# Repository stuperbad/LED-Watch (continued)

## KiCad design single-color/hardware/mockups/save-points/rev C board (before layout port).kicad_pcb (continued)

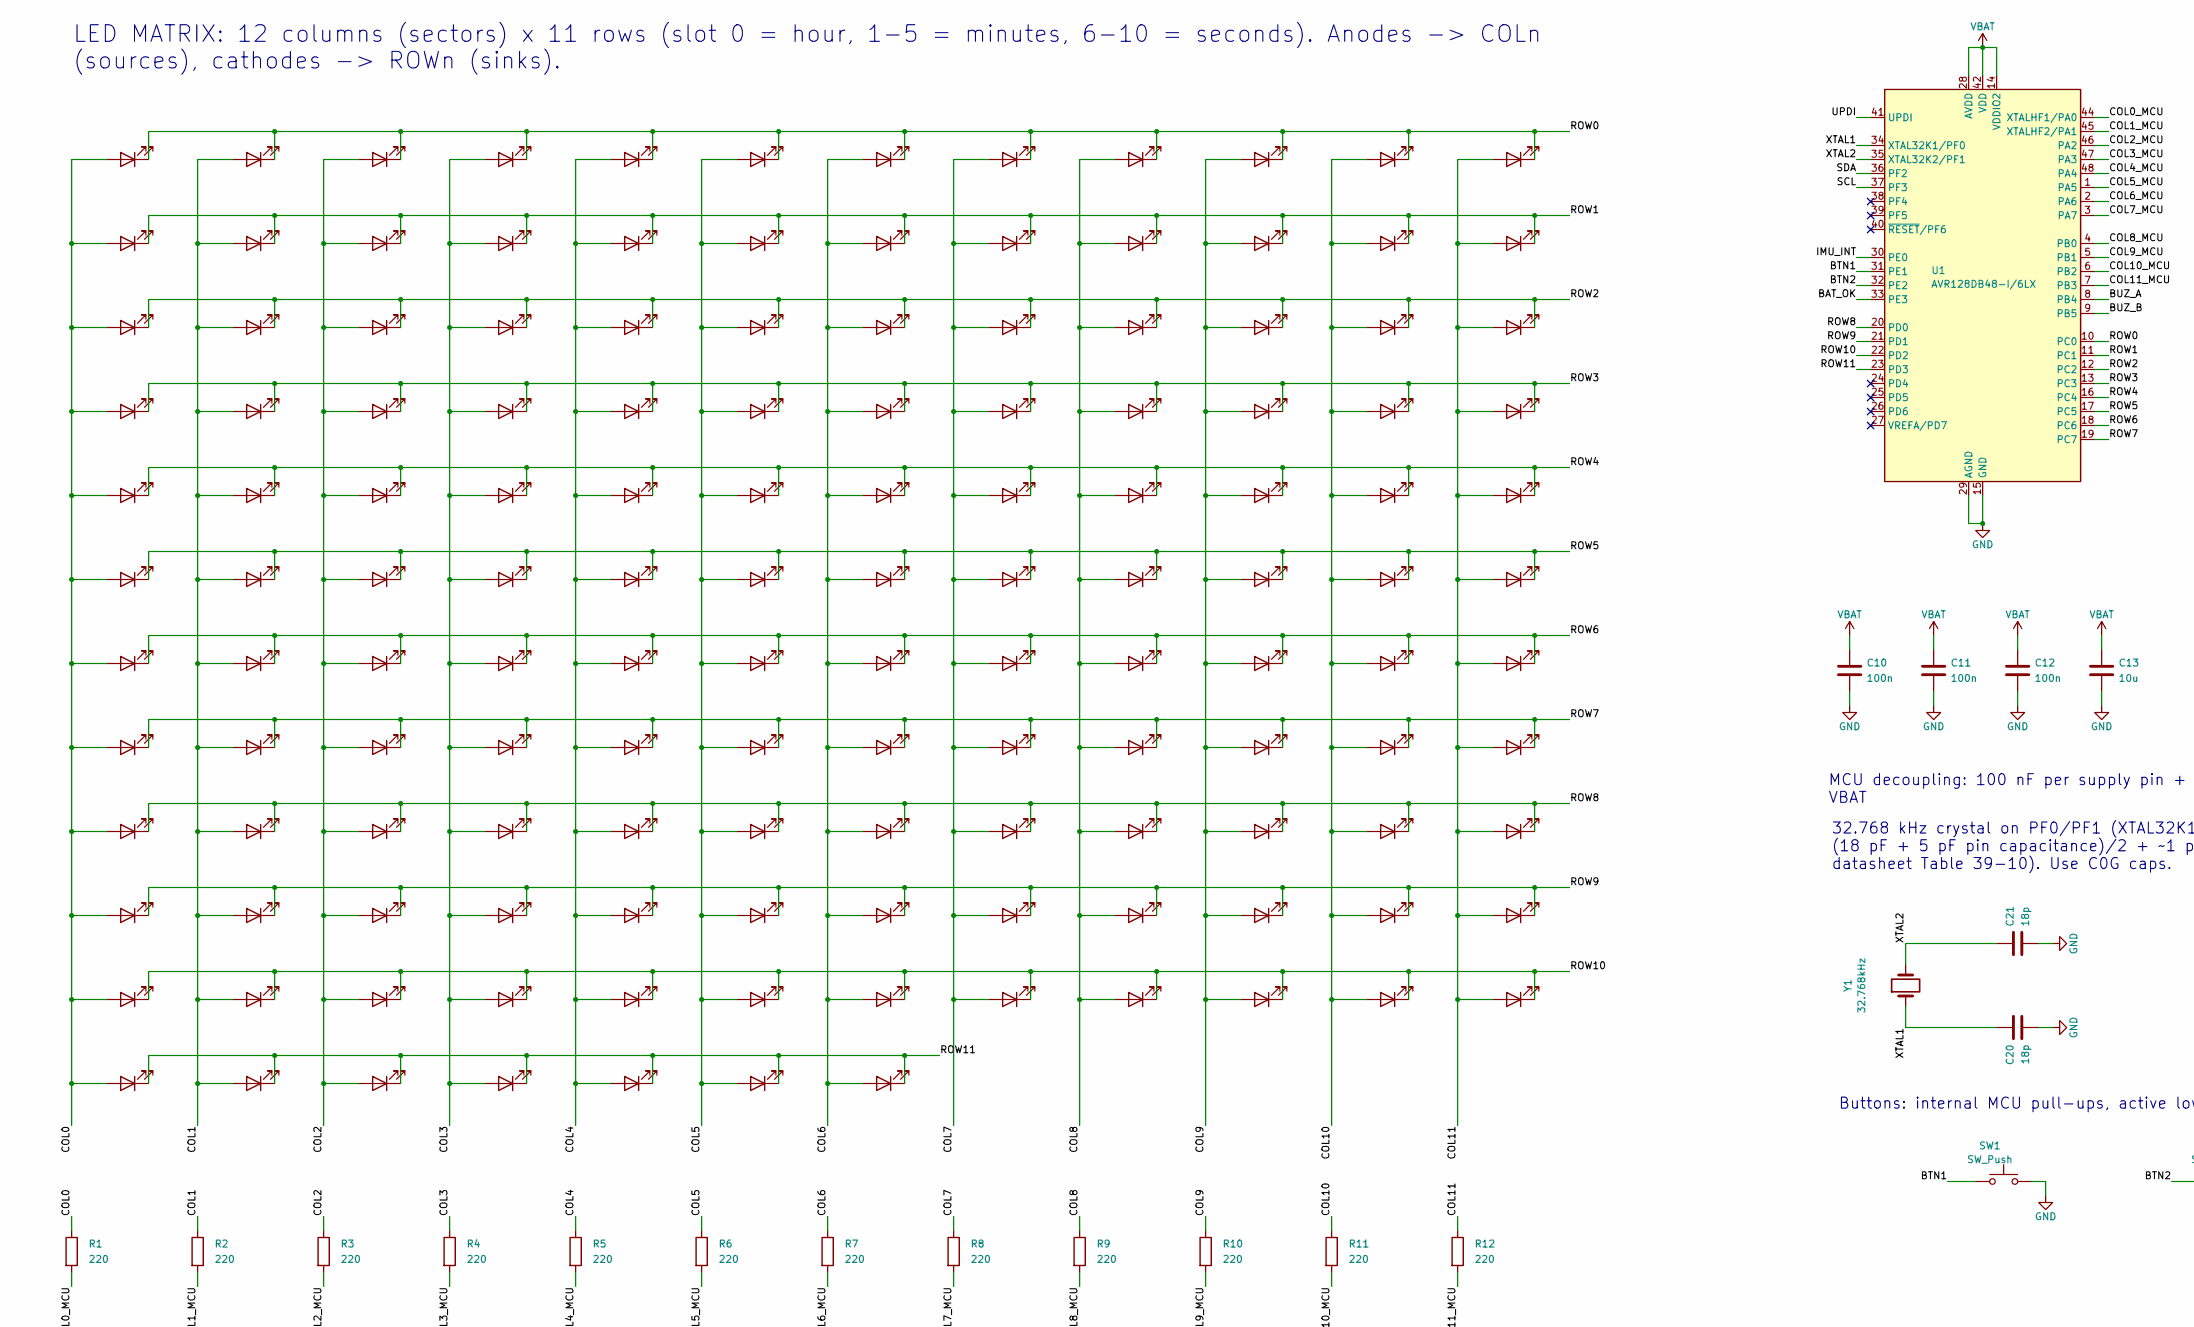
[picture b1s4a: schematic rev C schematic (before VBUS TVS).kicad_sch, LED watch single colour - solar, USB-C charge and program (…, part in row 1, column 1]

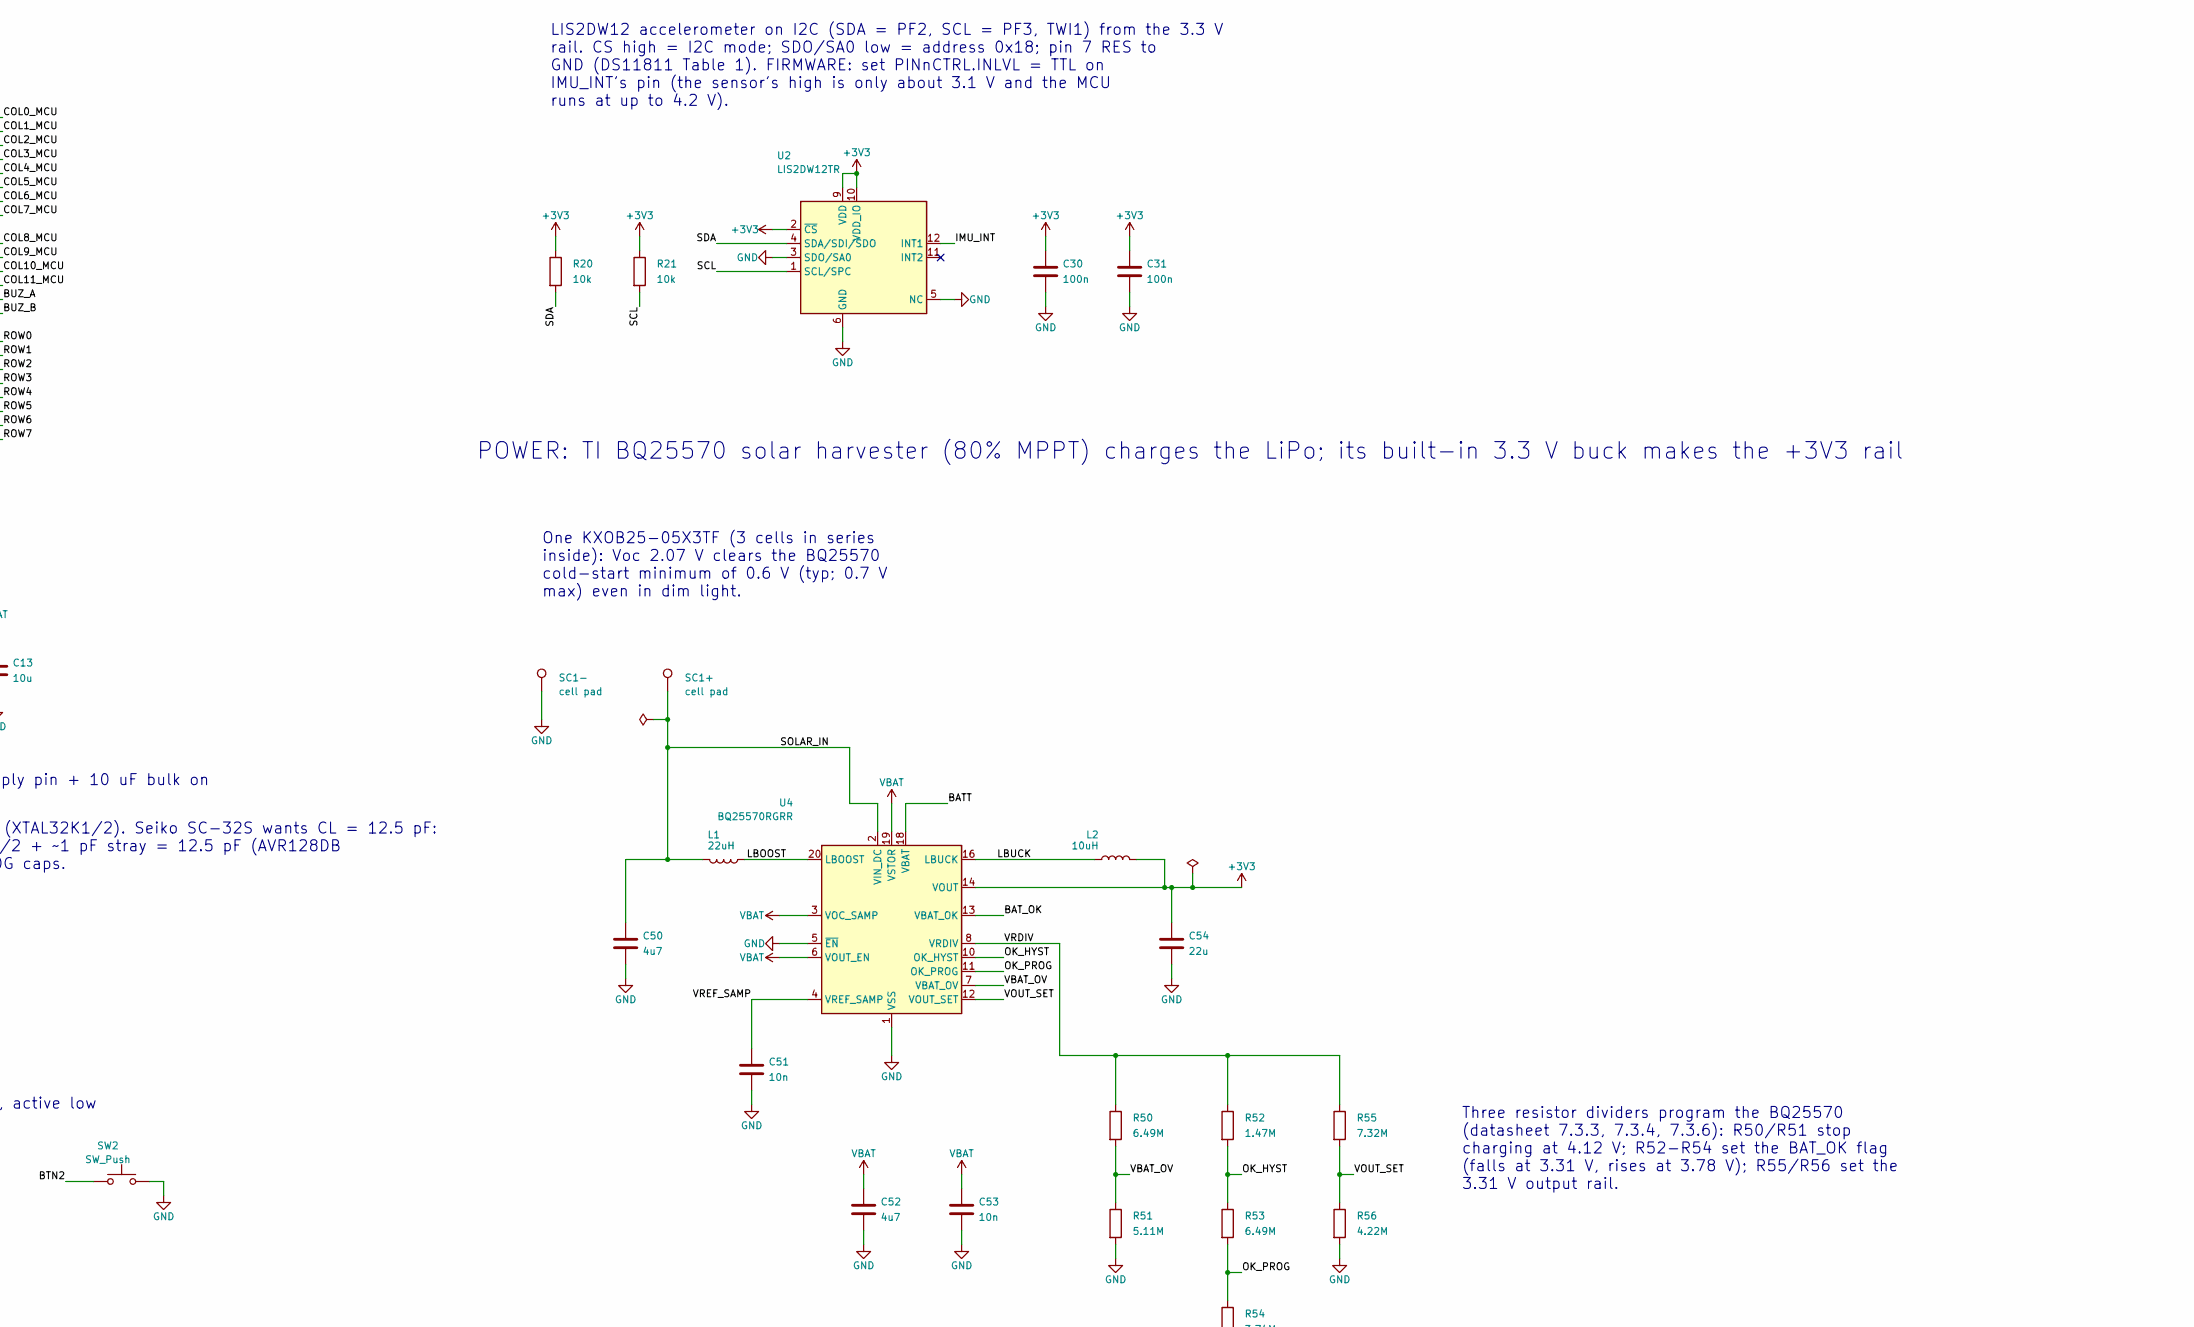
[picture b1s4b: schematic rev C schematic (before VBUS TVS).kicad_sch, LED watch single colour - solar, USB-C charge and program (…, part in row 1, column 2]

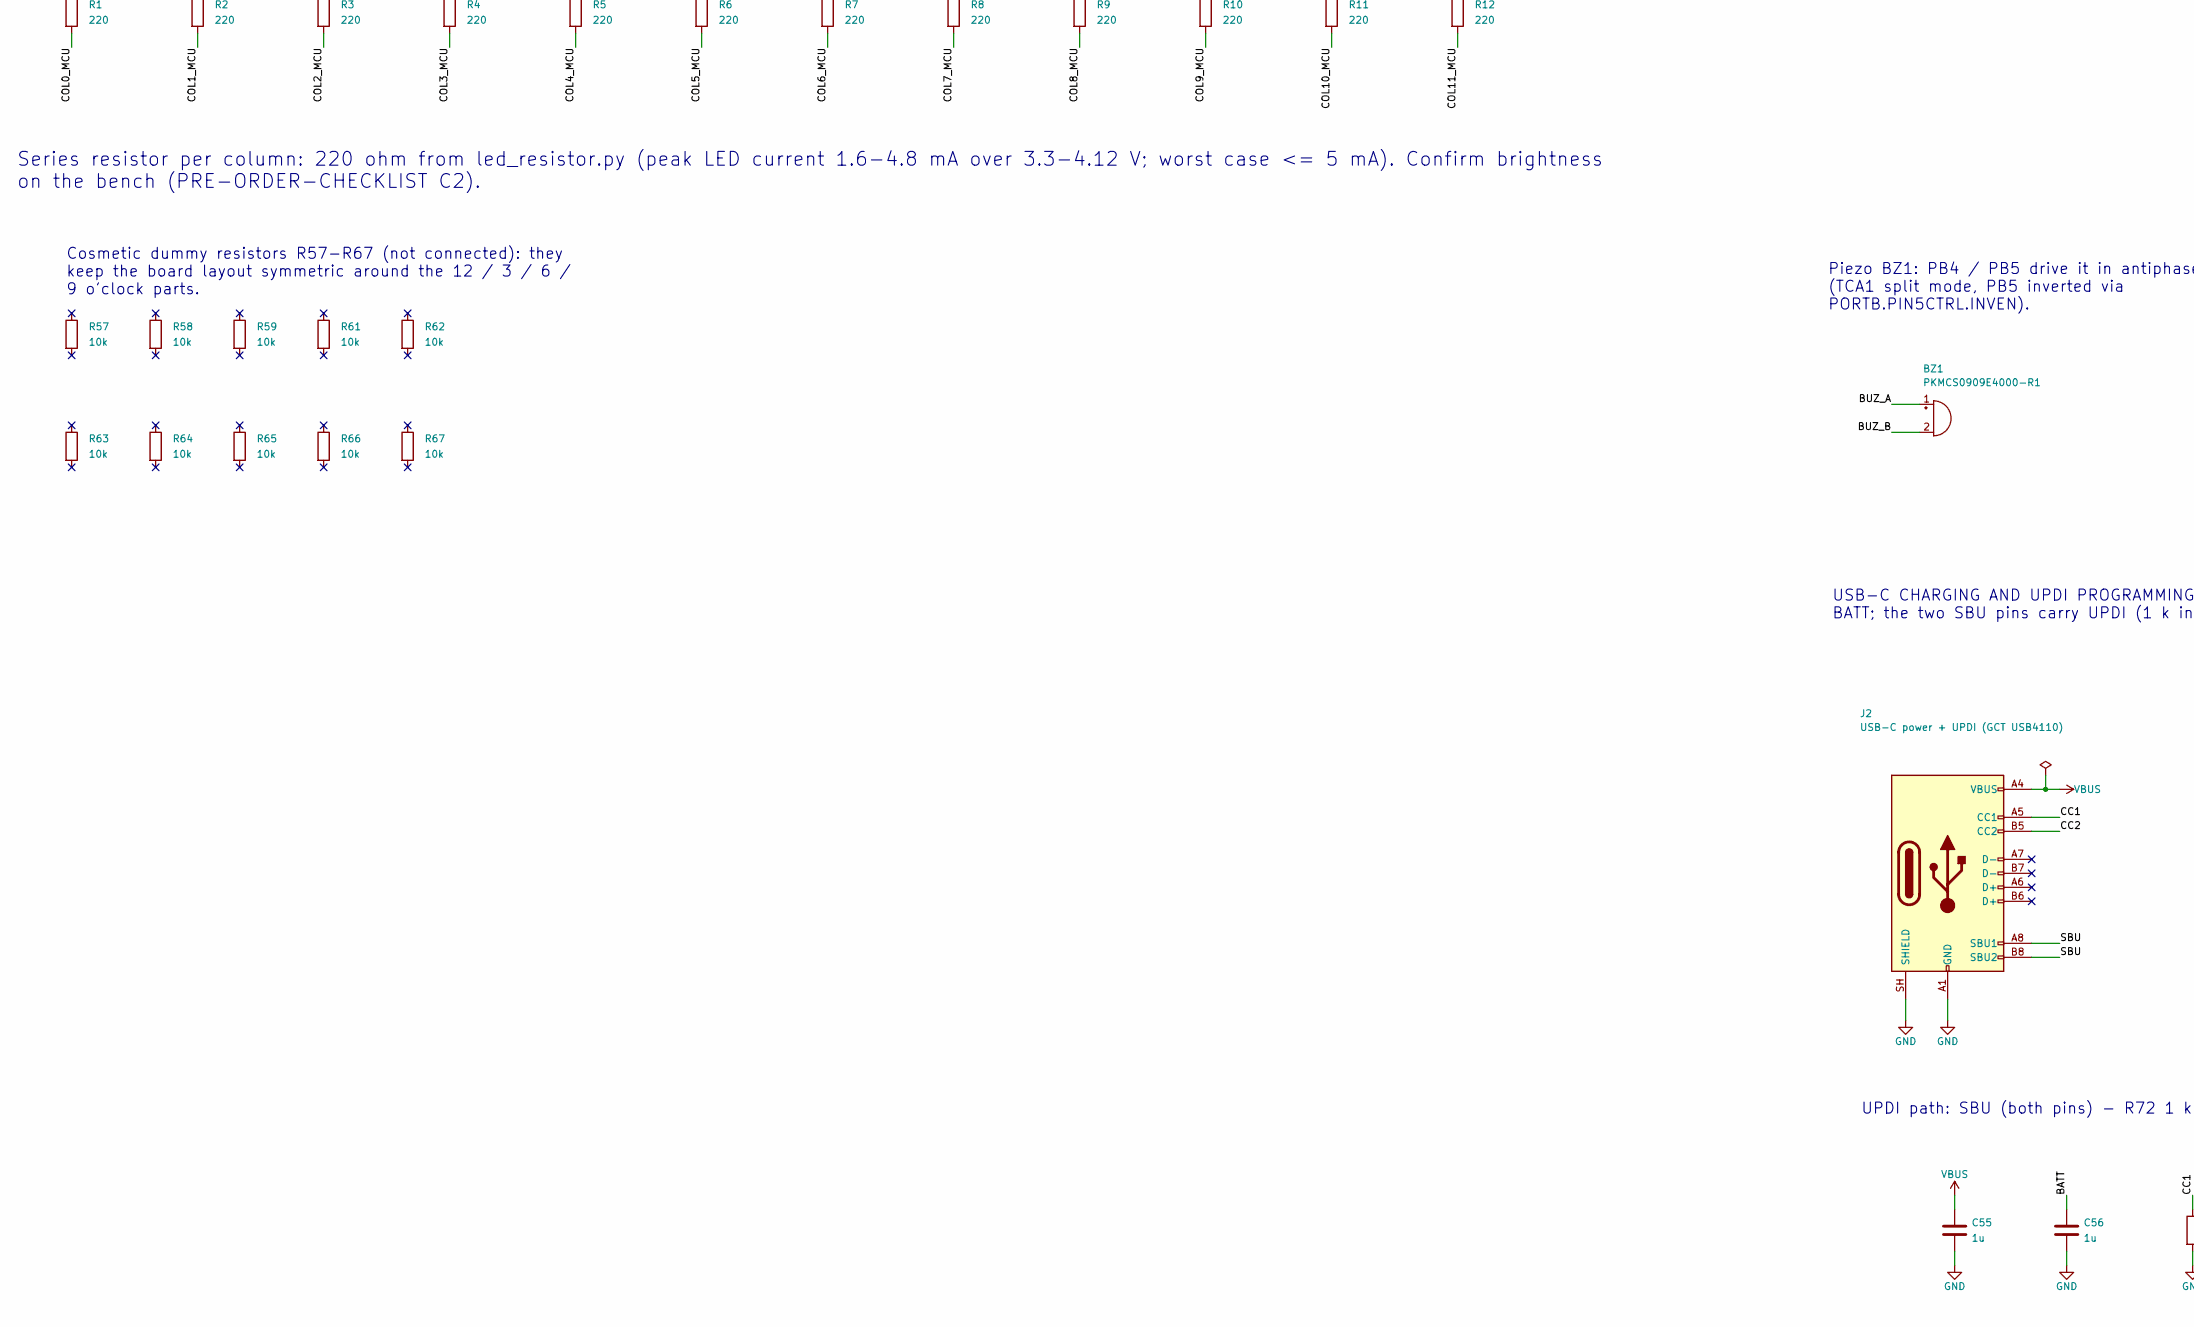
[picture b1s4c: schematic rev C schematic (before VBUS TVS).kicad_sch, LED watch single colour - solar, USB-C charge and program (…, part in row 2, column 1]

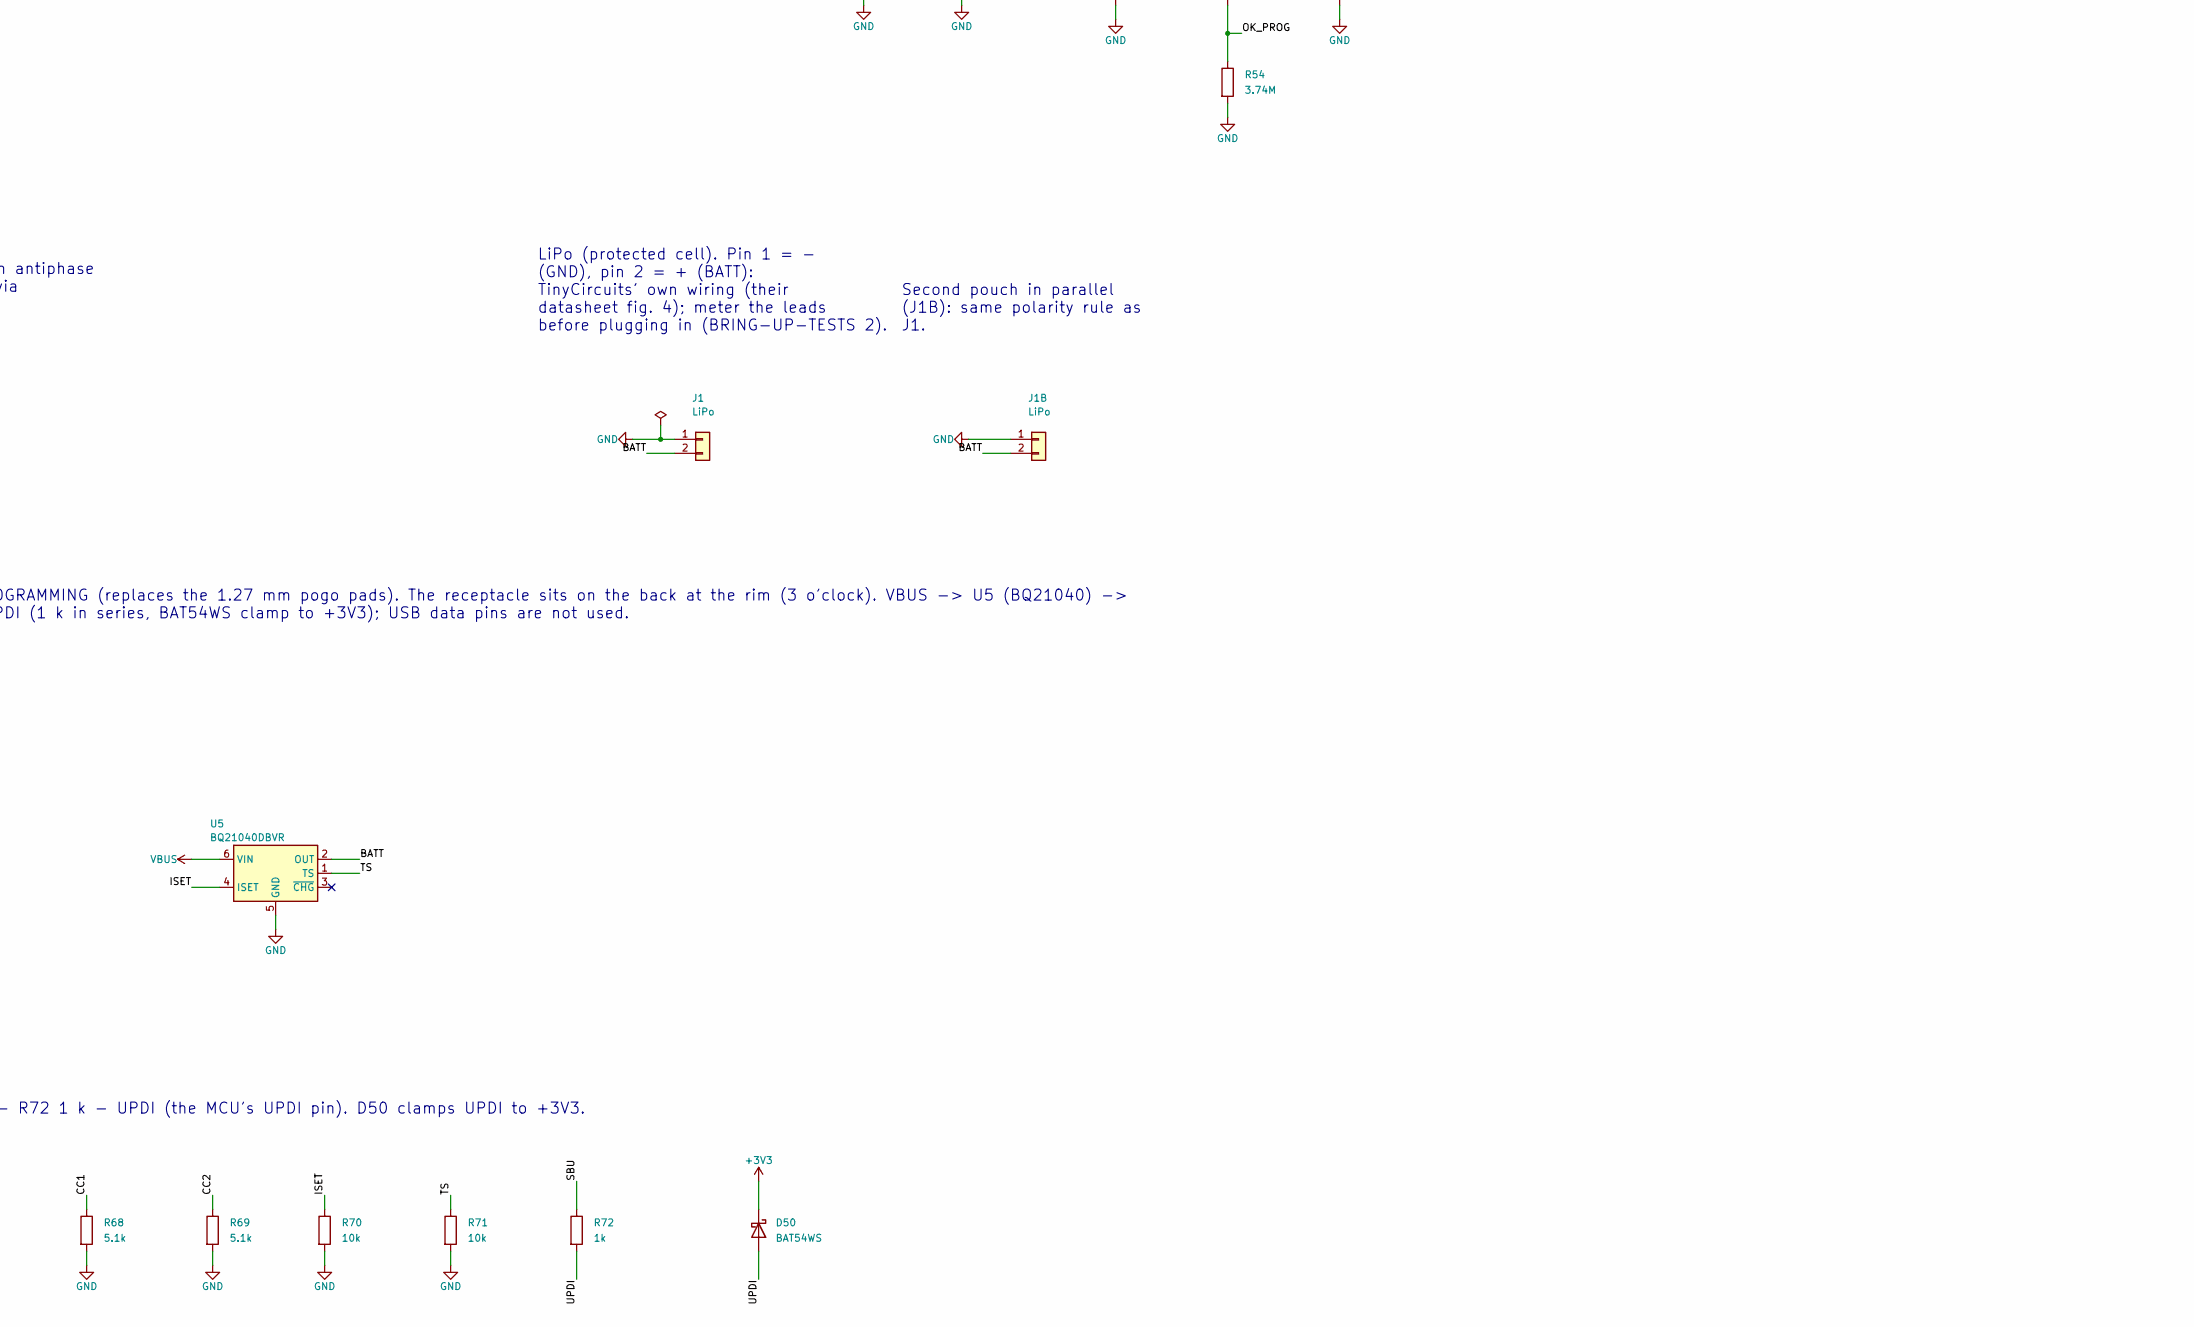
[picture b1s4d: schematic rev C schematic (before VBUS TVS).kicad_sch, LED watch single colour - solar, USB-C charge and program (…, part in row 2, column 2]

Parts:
BZ1: PKMCS0909E4000-R1; Piezo_Murata_PKMCS0909E4000-R1_9x9mm; MPN PKMCS0909E4000-R1; LCSC C910763
C10, C11, C12, C30, C31: 100n; C_0402_1005Metric
C13: 10u; C_0402_1005Metric
C20, C21: 18p; C_0402_1005Metric
C50, C52: 4u7; C_0402_1005Metric
C51, C53: 10n; C_0402_1005Metric
C54: 22u; C_0805_2012Metric
C55, C56: 1u; C_0402_1005Metric; LCSC C52923
D50: BAT54WS; D_SOD-323; MPN BAT54WS; LCSC C304155
H1, H2, H3, H4, H5, H6, H7, H8, H9, H10, H11, H12: LED white 0603; LED_0603_1608Metric
IND1: SET; LED_0402_1005Metric
IND2: TMR; LED_0402_1005Metric
IND3: BAT; LED_0402_1005Metric
IND4: FUN; LED_0402_1005Metric
IND5: CFG; LED_0402_1005Metric
IND6: LCK; LED_0402_1005Metric
IND7: ALM; LED_0402_1005Metric
J1, J1B: LiPo; JST_SH_SM02B-SRSS-TB_1x02-1MP_P1.00mm_Horizontal
J2: USB-C power + UPDI (GCT USB4110); USB_C_Receptacle_GCT_USB4110; MPN USB4110-GF-A
L1: 22uH; L_1210_3225Metric
L2: 10uH; L_1210_3225Metric
M0, M1, M2, M3, M4, M5, M6, M7, M8, M9, M10, M11, M12, M13, M14, M15, M16, M17, M18, M19, M20, M21, M22, M23, M24, M25, M26, M27, M28, M29, M30, M31, M32, M33, M34, M35, M36, M37, M38, M39, M40, M41, M42, M43, M44, M45, M46, M47, M48, M49, M50, M51, M52, M53, M54, M55, M56, M57, M58, M59: LED white 0402; LED_0402_1005Metric
R1, R2, R3, R4, R5, R6, R7, R8, R9, R10, R11, R12: 220; R_0402_1005Metric
R20, R21, R57, R58, R59, R61, R62, R63, R64, R65, R66, R67: 10k; R_0402_1005Metric
R50, R53: 6.49M; R_0402_1005Metric
R51: 5.11M; R_0402_1005Metric
R52: 1.47M; R_0402_1005Metric
R54: 3.74M; R_0402_1005Metric
R55: 7.32M; R_0402_1005Metric
R56: 4.22M; R_0402_1005Metric
R68, R69: 5.1k; R_0402_1005Metric; LCSC C25905
R70, R71: 10k; R_0402_1005Metric; LCSC C25744
R72: 1k; R_0402_1005Metric; LCSC C11702
S0, S1, S2, S3, S4, S5, S6, S7, S8, S9, S10, S11, S12, S13, S14, S15, S16, S17, S18, S19, S20, S21, S22, S23, S24, S25, S26, S27, S28, S29, S30, S31, S32, S33, S34, S35, S36, S37, S38, S39, S40, S41, S42, S43, S44, S45, S46, S47, S48, S49, S50, S51, S52, S53, S54, S55, S56, S57, S58, S59: LED white 0201; LED_0201_0603Metric
SC1+, SC1-: cell pad; KXOB25_cell_pad_2.5x7.4mm
SW1, SW2: SW_Push; SW_Push_1P1T_NO_CK_KMR2
U1: AVR128DB48-I/6LX; QFN-48-1EP_6x6mm_P0.4mm_EP4.2x4.2mm
U2: LIS2DW12TR; LGA-12_2x2mm_P0.5mm; MPN LIS2DW12TR
U4: BQ25570RGRR; BQ25570RGR_VQFN-20_3.5x3.5mm_P0.5mm_EP2.05mm
U5: BQ21040DBVR; SOT-23-6; MPN BQ21040DBVR; LCSC C202311
Y1: 32.768kHz; Crystal_SMD_3215-2Pin_3.2x1.5mm; MPN ABS07-32.768KHZ-T

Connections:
+3V3: C30.1, C31.1, C54.1, D50.1 (K), L2.2, R20.1, R21.1, U2.2 (~CS), U2.9 (VDD), U2.10 (VDD_IO), U4.14 (VOUT)
/BATT: C56.1, J1.2, J1B.2, U4.18 (VBAT), U5.2 (OUT)
/BAT_OK: U1.33 (PE3), U4.13 (VBAT_OK)
/BTN1: SW1.1, U1.31 (PE1)
/BTN2: SW2.1, U1.32 (PE2)
/BUZ_A: BZ1.1 (+), U1.8 (PB4)
/BUZ_B: BZ1.2 (-), U1.9 (PB5)
/CC1: J2.A5 (CC1), R68.1
/CC2: J2.B5 (CC2), R69.1
/COL0: H12.2 (A), IND1.2 (A), M0.2 (A), M1.2 (A), M2.2 (A), M3.2 (A), M4.2 (A), R1.1, S0.2 (A), S1.2 (A), S2.2 (A), S3.2 (A), S4.2 (A)
/COL0_MCU: R1.2, U1.44 (XTALHF1/PA0)
/COL1: H1.2 (A), IND2.2 (A), M5.2 (A), M6.2 (A), M7.2 (A), M8.2 (A), M9.2 (A), R2.1, S5.2 (A), S6.2 (A), S7.2 (A), S8.2 (A), S9.2 (A)
/COL1_MCU: R2.2, U1.45 (XTALHF2/PA1)
/COL2: H2.2 (A), IND3.2 (A), M10.2 (A), M11.2 (A), M12.2 (A), M13.2 (A), M14.2 (A), R3.1, S10.2 (A), S11.2 (A), S12.2 (A), S13.2 (A), S14.2 (A)
/COL2_MCU: R3.2, U1.46 (PA2)
/COL3: H3.2 (A), IND4.2 (A), M15.2 (A), M16.2 (A), M17.2 (A), M18.2 (A), M19.2 (A), R4.1, S15.2 (A), S16.2 (A), S17.2 (A), S18.2 (A), S19.2 (A)
/COL3_MCU: R4.2, U1.47 (PA3)
/COL4: H4.2 (A), IND5.2 (A), M20.2 (A), M21.2 (A), M22.2 (A), M23.2 (A), M24.2 (A), R5.1, S20.2 (A), S21.2 (A), S22.2 (A), S23.2 (A), S24.2 (A)
/COL4_MCU: R5.2, U1.48 (PA4)
/COL5: H5.2 (A), IND6.2 (A), M25.2 (A), M26.2 (A), M27.2 (A), M28.2 (A), M29.2 (A), R6.1, S25.2 (A), S26.2 (A), S27.2 (A), S28.2 (A), S29.2 (A)
/COL5_MCU: R6.2, U1.1 (PA5)
/COL6: H6.2 (A), IND7.2 (A), M30.2 (A), M31.2 (A), M32.2 (A), M33.2 (A), M34.2 (A), R7.1, S30.2 (A), S31.2 (A), S32.2 (A), S33.2 (A), S34.2 (A)
/COL6_MCU: R7.2, U1.2 (PA6)
/COL7: H7.2 (A), M35.2 (A), M36.2 (A), M37.2 (A), M38.2 (A), M39.2 (A), R8.1, S35.2 (A), S36.2 (A), S37.2 (A), S38.2 (A), S39.2 (A)
/COL7_MCU: R8.2, U1.3 (PA7)
/COL8: H8.2 (A), M40.2 (A), M41.2 (A), M42.2 (A), M43.2 (A), M44.2 (A), R9.1, S40.2 (A), S41.2 (A), S42.2 (A), S43.2 (A), S44.2 (A)
/COL8_MCU: R9.2, U1.4 (PB0)
/COL9: H9.2 (A), M45.2 (A), M46.2 (A), M47.2 (A), M48.2 (A), M49.2 (A), R10.1, S45.2 (A), S46.2 (A), S47.2 (A), S48.2 (A), S49.2 (A)
/COL9_MCU: R10.2, U1.5 (PB1)
/COL10: H10.2 (A), M50.2 (A), M51.2 (A), M52.2 (A), M53.2 (A), M54.2 (A), R11.1, S50.2 (A), S51.2 (A), S52.2 (A), S53.2 (A), S54.2 (A)
/COL10_MCU: R11.2, U1.6 (PB2)
/COL11: H11.2 (A), M55.2 (A), M56.2 (A), M57.2 (A), M58.2 (A), M59.2 (A), R12.1, S55.2 (A), S56.2 (A), S57.2 (A), S58.2 (A), S59.2 (A)
/COL11_MCU: R12.2, U1.7 (PB3)
/IMU_INT: U1.30 (PE0), U2.12 (INT1)
/ISET: R70.1, U5.4 (ISET)
/LBOOST: L1.1, U4.20 (LBOOST)
/LBUCK: L2.1, U4.16 (LBUCK)
/OK_HYST: R52.2, R53.1, U4.10 (OK_HYST)
/OK_PROG: R53.2, R54.1, U4.11 (OK_PROG)
/ROW0: H1.1 (K), H2.1 (K), H3.1 (K), H4.1 (K), H5.1 (K), H6.1 (K), H7.1 (K), H8.1 (K), H9.1 (K), H10.1 (K), H11.1 (K), H12.1 (K), U1.10 (PC0)
/ROW1: M0.1 (K), M5.1 (K), M10.1 (K), M15.1 (K), M20.1 (K), M25.1 (K), M30.1 (K), M35.1 (K), M40.1 (K), M45.1 (K), M50.1 (K), M55.1 (K), U1.11 (PC1)
/ROW2: M1.1 (K), M6.1 (K), M11.1 (K), M16.1 (K), M21.1 (K), M26.1 (K), M31.1 (K), M36.1 (K), M41.1 (K), M46.1 (K), M51.1 (K), M56.1 (K), U1.12 (PC2)
/ROW3: M2.1 (K), M7.1 (K), M12.1 (K), M17.1 (K), M22.1 (K), M27.1 (K), M32.1 (K), M37.1 (K), M42.1 (K), M47.1 (K), M52.1 (K), M57.1 (K), U1.13 (PC3)
/ROW4: M3.1 (K), M8.1 (K), M13.1 (K), M18.1 (K), M23.1 (K), M28.1 (K), M33.1 (K), M38.1 (K), M43.1 (K), M48.1 (K), M53.1 (K), M58.1 (K), U1.16 (PC4)
/ROW5: M4.1 (K), M9.1 (K), M14.1 (K), M19.1 (K), M24.1 (K), M29.1 (K), M34.1 (K), M39.1 (K), M44.1 (K), M49.1 (K), M54.1 (K), M59.1 (K), U1.17 (PC5)
/ROW6: S0.1 (K), S5.1 (K), S10.1 (K), S15.1 (K), S20.1 (K), S25.1 (K), S30.1 (K), S35.1 (K), S40.1 (K), S45.1 (K), S50.1 (K), S55.1 (K), U1.18 (PC6)
/ROW7: S1.1 (K), S6.1 (K), S11.1 (K), S16.1 (K), S21.1 (K), S26.1 (K), S31.1 (K), S36.1 (K), S41.1 (K), S46.1 (K), S51.1 (K), S56.1 (K), U1.19 (PC7)
/ROW8: S2.1 (K), S7.1 (K), S12.1 (K), S17.1 (K), S22.1 (K), S27.1 (K), S32.1 (K), S37.1 (K), S42.1 (K), S47.1 (K), S52.1 (K), S57.1 (K), U1.20 (PD0)
/ROW9: S3.1 (K), S8.1 (K), S13.1 (K), S18.1 (K), S23.1 (K), S28.1 (K), S33.1 (K), S38.1 (K), S43.1 (K), S48.1 (K), S53.1 (K), S58.1 (K), U1.21 (PD1)
/ROW10: S4.1 (K), S9.1 (K), S14.1 (K), S19.1 (K), S24.1 (K), S29.1 (K), S34.1 (K), S39.1 (K), S44.1 (K), S49.1 (K), S54.1 (K), S59.1 (K), U1.22 (PD2)
/ROW11: IND1.1 (K), IND2.1 (K), IND3.1 (K), IND4.1 (K), IND5.1 (K), IND6.1 (K), IND7.1 (K), U1.23 (PD3)
/SBU: J2.A8 (SBU1), J2.B8 (SBU2), R72.1
/SCL: R21.2, U1.37 (PF3), U2.1 (SCL/SPC)
/SDA: R20.2, U1.36 (PF2), U2.4 (SDA/SDI/SDO)
/SOLAR_IN: C50.1, L1.2, SC1+.1, U4.2 (VIN_DC)
/TS: R71.1, U5.1 (TS)
/UPDI: D50.2 (A), R72.2, U1.41 (UPDI)
/VBAT_OV: R50.2, R51.1, U4.7 (VBAT_OV)
/VOUT_SET: R55.2, R56.1, U4.12 (VOUT_SET)
/VRDIV: R50.1, R52.1, R55.1, U4.8 (VRDIV)
/VREF_SAMP: C51.1, U4.4 (VREF_SAMP)
/XTAL1: C20.1, U1.34 (XTAL32K1/PF0), Y1.1
/XTAL2: C21.1, U1.35 (XTAL32K2/PF1), Y1.2
GND: C10.2, C11.2, C12.2, C13.2, C20.2, C21.2, C30.2, C31.2, C50.2, C51.2, C52.2, C53.2, C54.2, C55.2, C56.2, J1.1, J1B.1, J2.A1 (GND), J2.A12 (GND), J2.B1 (GND), J2.B12 (GND), J2.SH (SHIELD), R51.2, R54.2, R56.2, R68.2, R69.2, R70.2, R71.2, SC1-.1, SW1.2, SW2.2, U1.15 (GND), U1.29 (AGND), U1.43 (GND), U1.49 (GND), U2.3 (SDO/SA0), U2.5 (NC), U2.6 (GND), U2.7 (RES), U2.8 (GND), U4.1 (VSS), U4.5 (~EN), U4.9 (VSS), U4.15 (VSS), U4.17 (VSS), U4.21 (VSS), U5.5 (GND); also elsewhere on the board
VBAT: C10.1, C11.1, C12.1, C13.1, C52.1, C53.1, U1.14 (VDDIO2), U1.28 (AVDD), U1.42 (VDD), U4.3 (VOC_SAMP), U4.6 (VOUT_EN), U4.19 (VSTOR)
VBUS: C55.1, J2.A4 (VBUS), J2.A9 (VBUS), J2.B4 (VBUS), J2.B9 (VBUS), U5.6 (VIN); also elsewhere on the board

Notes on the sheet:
LiPo (protected cell). Pin 1 = - (GND), pin 2 = + (BATT): TinyCircuits' own wiring (their datasheet fig. 4); meter the leads before plugging in (BRING-UP-TESTS 2).
UPDI path: SBU (both pins) - R72 1 k - UPDI (the MCU's UPDI pin). D50 clamps UPDI to +3V3.
MCU decoupling: 100 nF per supply pin + 10 uF bulk on VBAT
LED MATRIX: 12 columns (sectors) x 11 rows (slot 0 = hour, 1-5 = minutes, 6-10 = seconds). Anodes -> COLn (sources), cathodes -> ROWn (sinks).
POWER: TI BQ25570 solar harvester (80% MPPT) charges the LiPo; its built-in 3.3 V buck makes the +3V3 rail
LIS2DW12 accelerometer on I2C (SDA = PF2, SCL = PF3, TWI1) from the 3.3 V rail. CS high = I2C mode; SDO/SA0 low = address 0x18; pin 7 RES to GND (DS11811 Table 1). FIRMWARE: set PINnCTRL.INLVL = TTL on IMU_INT's pin (the sensor's high is only about 3.1 V and the MCU runs at up to 4.2 V).
Second pouch in parallel (J1B): same polarity rule as J1.
Series resistor per column: 220 ohm from led_resistor.py (peak LED current 1.6-4.8 mA over 3.3-4.12 V; worst case <= 5 mA). Confirm brightness on the bench (PRE-ORDER-CHECKLIST C2).
Piezo BZ1: PB4 / PB5 drive it in antiphase (TCA1 split mode, PB5 inverted via PORTB.PIN5CTRL.INVEN).
Three resistor dividers program the BQ25570 (datasheet 7.3.3, 7.3.4, 7.3.6): R50/R51 stop charging at 4.12 V; R52-R54 set the BAT_OK flag (falls at 3.31 V, rises at 3.78 V); R55/R56 set the 3.31 V output rail.
Cosmetic dummy resistors R57-R67 (not connected): they keep the board layout symmetric around the 12 / 3 / 6 / 9 o'clock parts.
USB-C CHARGING AND UPDI PROGRAMMING (replaces the 1.27 mm pogo pads). The receptacle sits on the back at the rim (3 o'clock). VBUS -> U5 (BQ21040) -> BATT; the two SBU pins carry UPDI (1 k in series, BAT54WS clamp to +3V3); USB data pins are not used.
One KXOB25-05X3TF (3 cells in series inside): Voc 2.07 V clears the BQ25570 cold-start minimum of 0.6 V (typ; 0.7 V max) even in dim light.
Buttons: internal MCU pull-ups, active low
32.768 kHz crystal on PF0/PF1 (XTAL32K1/2). Seiko SC-32S wants CL = 12.5 pF: (18 pF + 5 pF pin capacitance)/2 + ~1 pF stray = 12.5 pF (AVR128DB datasheet Table 39-10). Use C0G caps.

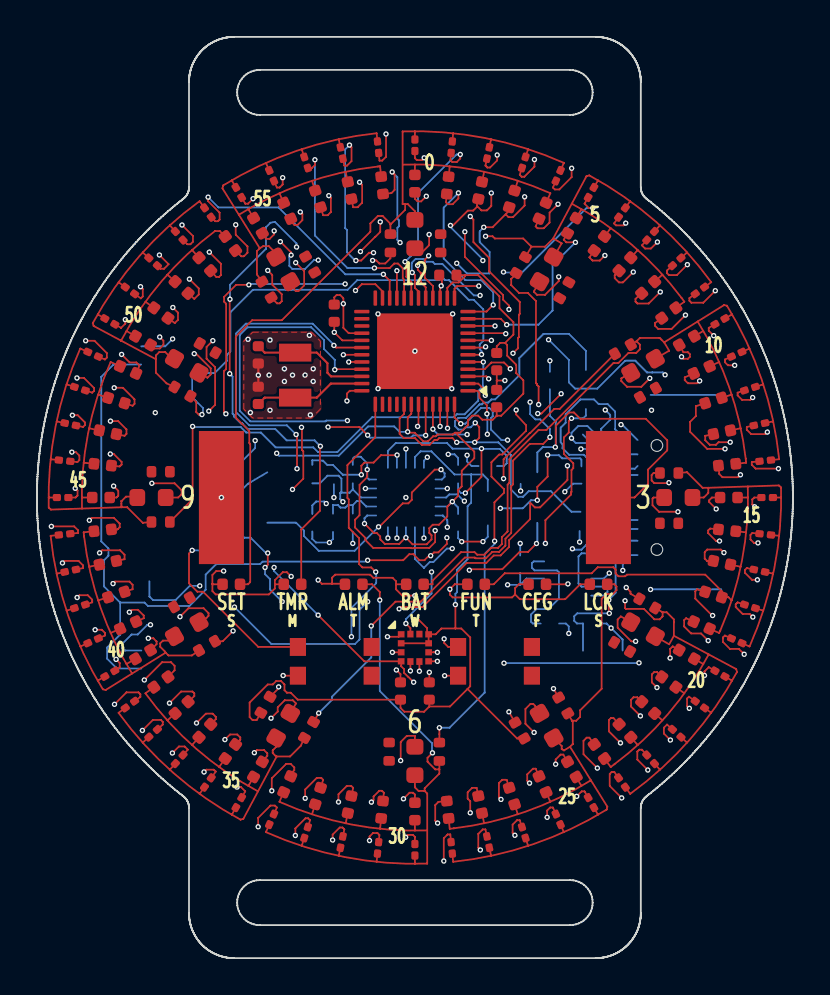
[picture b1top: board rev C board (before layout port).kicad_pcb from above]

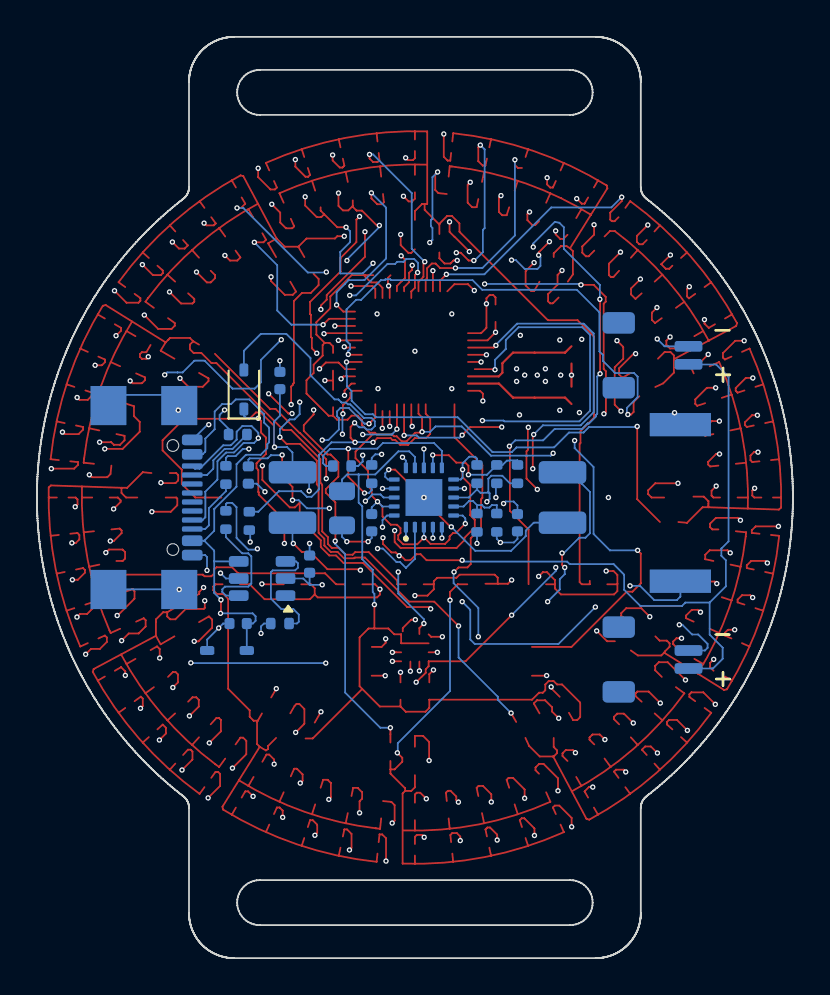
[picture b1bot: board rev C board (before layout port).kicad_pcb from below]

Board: 4 copper layers, 42.0 x 51.2 mm, 207 parts (29 on the bottom side), 66 nets.

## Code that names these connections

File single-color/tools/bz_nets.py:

"""Wire the piezo BZ1 to the two spare MCU pins PB4 (pad 8) and PB5 (pad 9): nets /BUZ_A and /BUZ_B.  usage (KiCad python): bz_nets.py in out"""
import sys

import pcbnew

b = pcbnew.LoadBoard(sys.argv[1])
fp = {f.GetReference(): f for f in b.GetFootprints()}
for p in fp["U1"].Pads():
    if p.GetNumber() in ("8", "9"):
        assert not p.GetNetname(), "U1 pad %s already has net %s" % (p.GetNumber(), p.GetNetname())
for n in ("/BUZ_A", "/BUZ_B"):
    if not b.FindNet(n):
        b.Add(pcbnew.NETINFO_ITEM(b, n))
for ref, pad, net in (("U1", "8", "/BUZ_A"), ("U1", "9", "/BUZ_B"), ("BZ1", "1", "/BUZ_A"), ("BZ1", "2", "/BUZ_B")):
    for p in fp[ref].Pads():
        if p.GetNumber() == pad:
            p.SetNet(b.FindNet(net))
pcbnew.SaveBoard(sys.argv[2], b)
print("U1 pads 8/9 and BZ1 pads 1/2 now on /BUZ_A and /BUZ_B")
